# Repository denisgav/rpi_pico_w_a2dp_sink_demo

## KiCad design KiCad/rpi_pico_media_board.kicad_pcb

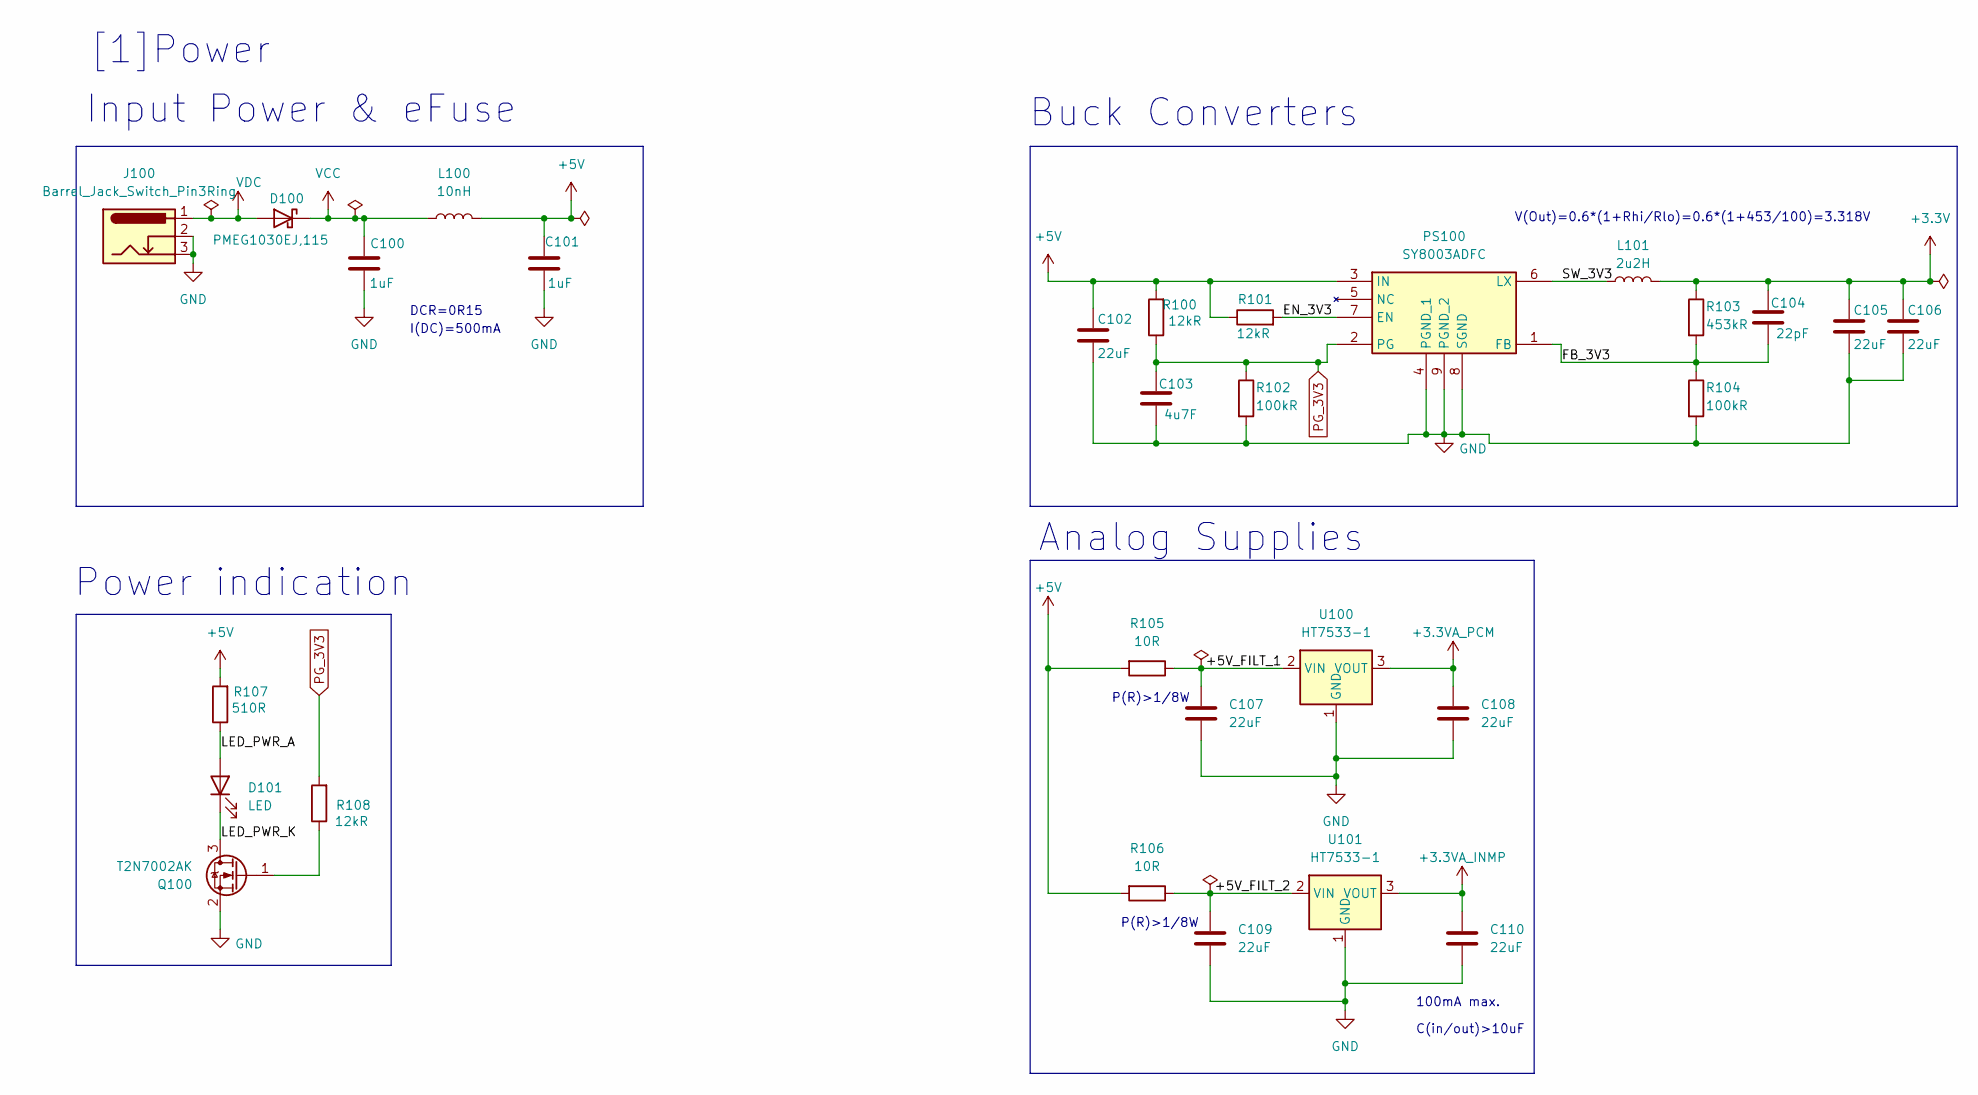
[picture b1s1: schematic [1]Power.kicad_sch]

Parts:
C100, C101: 1uF; C_0603_1608Metric; Manufacturer Part Number CL10A105KB8NNNC
C102, C105, C106, C107, C108, C109, C110: 22uF; C_1206_3216Metric; Manufacturer Part Number CS3216X5R226M160NRI
C103: 4u7F; C_0603_1608Metric; Manufacturer Part Number CL10A475KP8NNNC
C104: 22pF; C_0603_1608Metric; Manufacturer Part Number CL10C220JB8NNNC
D100: PMEG1030EJ,115; D_SOD-323F; Manufacturer Part Number PMEG1030EJ,115
D101: LED; LED_0603_1608Metric; Manufacturer Part Number XL-1608SURC-06
J100: Barrel_Jack_Switch_Pin3Ring; BarrelJack_GCT_DCJ200-10-A_Horizontal; Manufacturer Part Number DC005
L100: 10nH; L_0603_1608Metric; Manufacturer Part Number LQW18AN10NG10D
L101: 2u2H; L_1008_2520Metric; Manufacturer Part Number DFE252012F-2R2M=P2
PS100: SY8003ADFC; SON50P200X200X65-9N; Manufacturer Part Number SY8003ADFC
Q100: T2N7002AK; SOT-23; Manufacturer Part Number T2N7002AK,LM
R100, R101, R108: 12kR; R_0603_1608Metric; Manufacturer Part Number 0603WAF1202T5E
R102, R104: 100kR; R_0603_1608Metric; Manufacturer Part Number 0603WAF1003T5E
R103: 453kR; R_0603_1608Metric; Manufacturer Part Number 0603WAF4533T5E
R105, R106: 10R; R_0805_2012Metric; Manufacturer Part Number 0805W8F100JT5E
R107: 510R; R_0603_1608Metric; Manufacturer Part Number 0603WAF5100T5E
U100, U101: HT7533-1; SOT-89-3; Manufacturer Part Number HT7533-1

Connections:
+3.3V: C104.1, C105.1, C106.1, L101.2, R103.1; also elsewhere on the board
+3.3VA_INMP: C110.1, U101.3 (VOUT); also elsewhere on the board
+3.3VA_PCM: C108.1, U100.3 (VOUT); also elsewhere on the board
+5V: C101.1, C102.1, L100.2, PS100.3 (IN), R100.2, R101.1, R105.2, R106.2, R107.2; also elsewhere on the board
/[1]Power/+5V_FILT_1: C107.1, R105.1, U100.2 (VIN)
/[1]Power/+5V_FILT_2: C109.1, R106.1, U101.2 (VIN)
/[1]Power/EN_3V3: PS100.7 (EN), R101.2
/[1]Power/FB_3V3: C104.2, PS100.1 (FB), R103.2, R104.1
/[1]Power/LED_PWR_A: D101.2 (A), R107.1
/[1]Power/LED_PWR_K: D101.1 (K), Q100.3 (D)
/[1]Power/SW_3V3: L101.1, PS100.6 (LX)
GND: C100.2, C101.2, C102.2, C103.2, C105.2, C106.2, C107.2, C108.2, C109.2, C110.2, J100.2, J100.3, PS100.4 (PGND_1), PS100.8 (SGND), PS100.9 (PGND_2), Q100.2 (S), R102.2, R104.2, U100.1 (GND), U101.1 (GND); also elsewhere on the board
unnamed: Q100.1 (G), R108.1
PG_3V3: C103.1, PS100.2 (PG), R100.1, R102.1, R108.2
VCC: C100.1, D100.1 (K), L100.1; also elsewhere on the board
VDC: D100.2 (A), J100.1

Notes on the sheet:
Analog Supplies
Power indication
P(R)>1/8W
I(DC)=500mA
Input Power & eFuse
100mA max.
[1]Power
DCR=0R15
C(in/out)>10uF
V(Out)=0.6*(1+Rhi/Rlo)=0.6*(1+453/100)=3.318V
Buck Converters

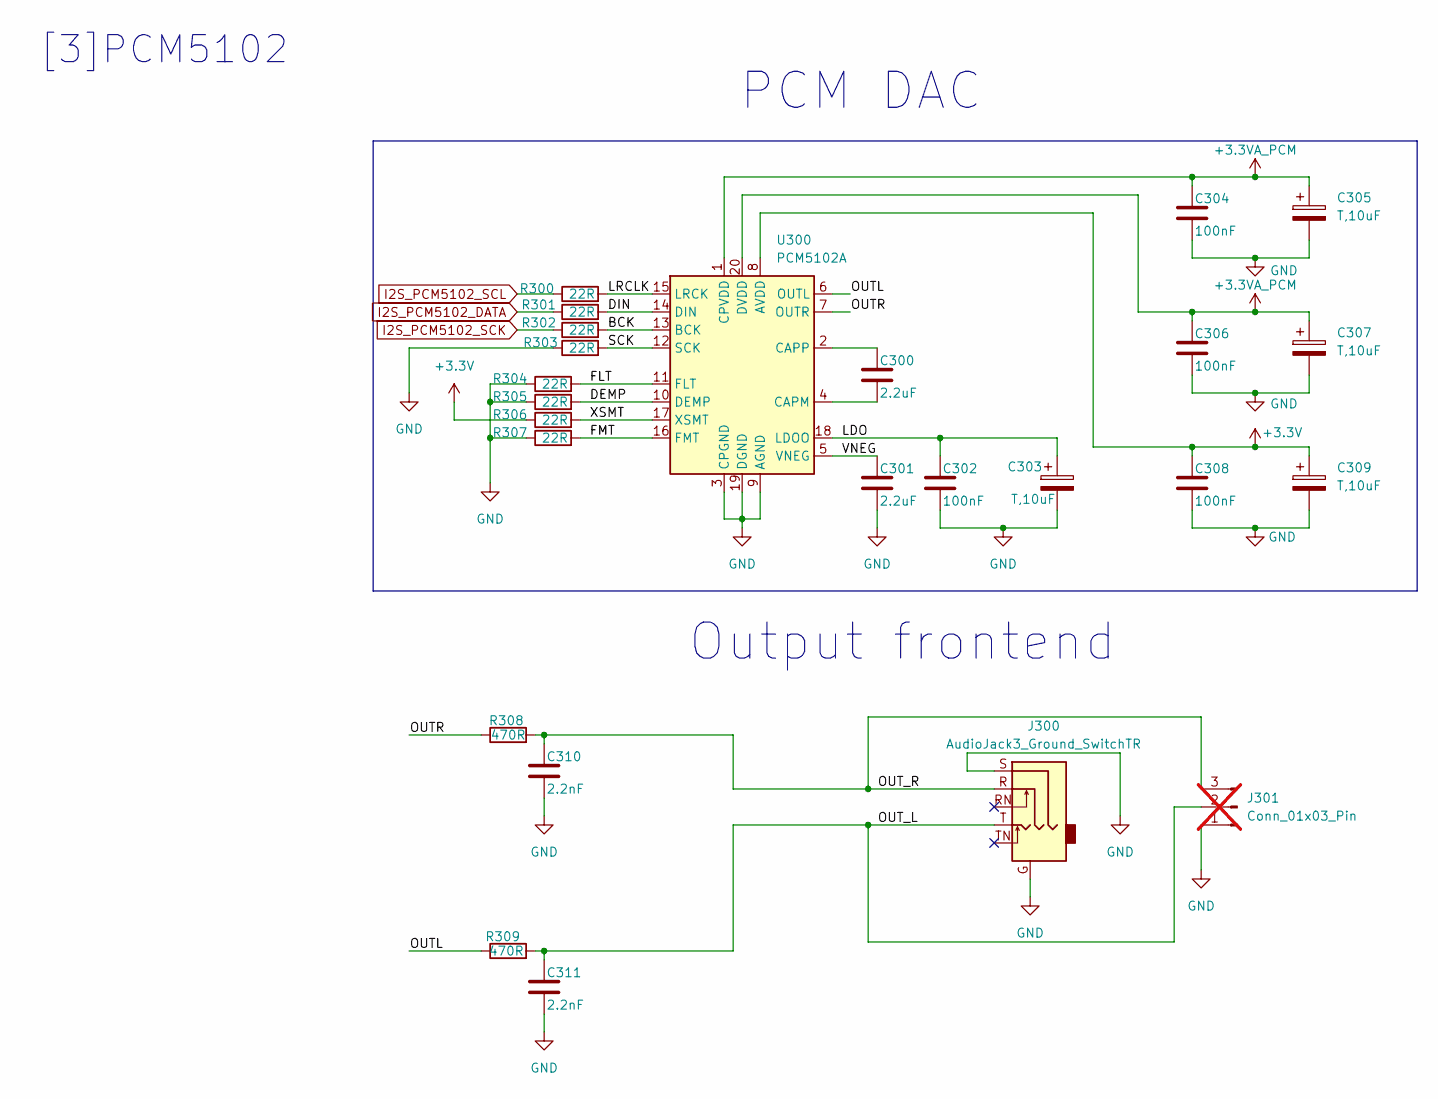
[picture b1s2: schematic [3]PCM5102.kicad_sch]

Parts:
C300, C301: 2.2uF; C_0603_1608Metric; Manufacturer Part Number CL10A225KA8NNNC
C302, C304, C306, C308: 100nF; C_0603_1608Metric; Manufacturer Part Number CL10B104KA8NNNC
C303, C305, C307, C309: T,10uF; CP_EIA-3216-18_Kemet-A; Manufacturer Part Number TAJA106K016RNJ
C310, C311: 2.2nF; C_0603_1608Metric; Manufacturer Part Number CL10B222KB8NNNC
J300: AudioJack3_Ground_SwitchTR; AudioJack_3.5mm_PJ311; Manufacturer Part Number PJ-342
J301: Conn_01x03_Pin; PinHeader_1x03_P2.54mm_Vertical; not fitted
R300, R301, R302, R303, R304, R305, R306, R307: 22R; R_0603_1608Metric; Manufacturer Part Number 0603WAF220JT5E
R308, R309: 470R; R_0805_2012Metric; Manufacturer Part Number ARG05FTC4700
U300: PCM5102A; TSSOP-20_4.4x6.5mm_P0.65mm; Manufacturer Part Number PCM5102AQPWRQ1

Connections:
+3.3V: C308.1, C309.1, R306.1, U300.8 (AVDD); also elsewhere on the board
+3.3VA_PCM: C304.1, C305.1, C306.1, C307.1, U300.1 (CPVDD), U300.20 (DVDD); also elsewhere on the board
/[3]PCM5102/BCK: R302.2, U300.13 (BCK)
/[3]PCM5102/DEMP: R305.2, U300.10 (DEMP)
/[3]PCM5102/DIN: R301.2, U300.14 (DIN)
/[3]PCM5102/FLT: R304.2, U300.11 (FLT)
/[3]PCM5102/FMT: R307.2, U300.16 (FMT)
/[3]PCM5102/LDO: C302.1, C303.1, U300.18 (LDOO)
/[3]PCM5102/LRCLK: R300.2, U300.15 (LRCK)
/[3]PCM5102/OUTL: R309.1, U300.6 (OUTL)
/[3]PCM5102/OUTR: R308.1, U300.7 (OUTR)
/[3]PCM5102/OUT_L: C311.1, J300.T, J301.2, R309.2
/[3]PCM5102/OUT_R: C310.1, J300.R, J301.3, R308.2
/[3]PCM5102/SCK: R303.2, U300.12 (SCK)
/[3]PCM5102/VNEG: C301.1, U300.5 (VNEG)
/[3]PCM5102/XSMT: R306.2, U300.17 (XSMT)
GND: C301.2, C302.2, C303.2, C304.2, C305.2, C306.2, C307.2, C308.2, C309.2, C310.2, C311.2, J300.G, J300.S, J301.1, R303.1, R304.1, R305.1, R307.1, U300.3 (CPGND), U300.9 (AGND), U300.19 (DGND); also elsewhere on the board
I2S_PCM5102_DATA: R301.1; also elsewhere on the board
I2S_PCM5102_SCK: R302.1; also elsewhere on the board
I2S_PCM5102_SCL: R300.1; also elsewhere on the board
unnamed: C300.2, U300.4 (CAPM)
unnamed: C300.1, U300.2 (CAPP)

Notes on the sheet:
[3]PCM5102
Output frontend
PCM DAC

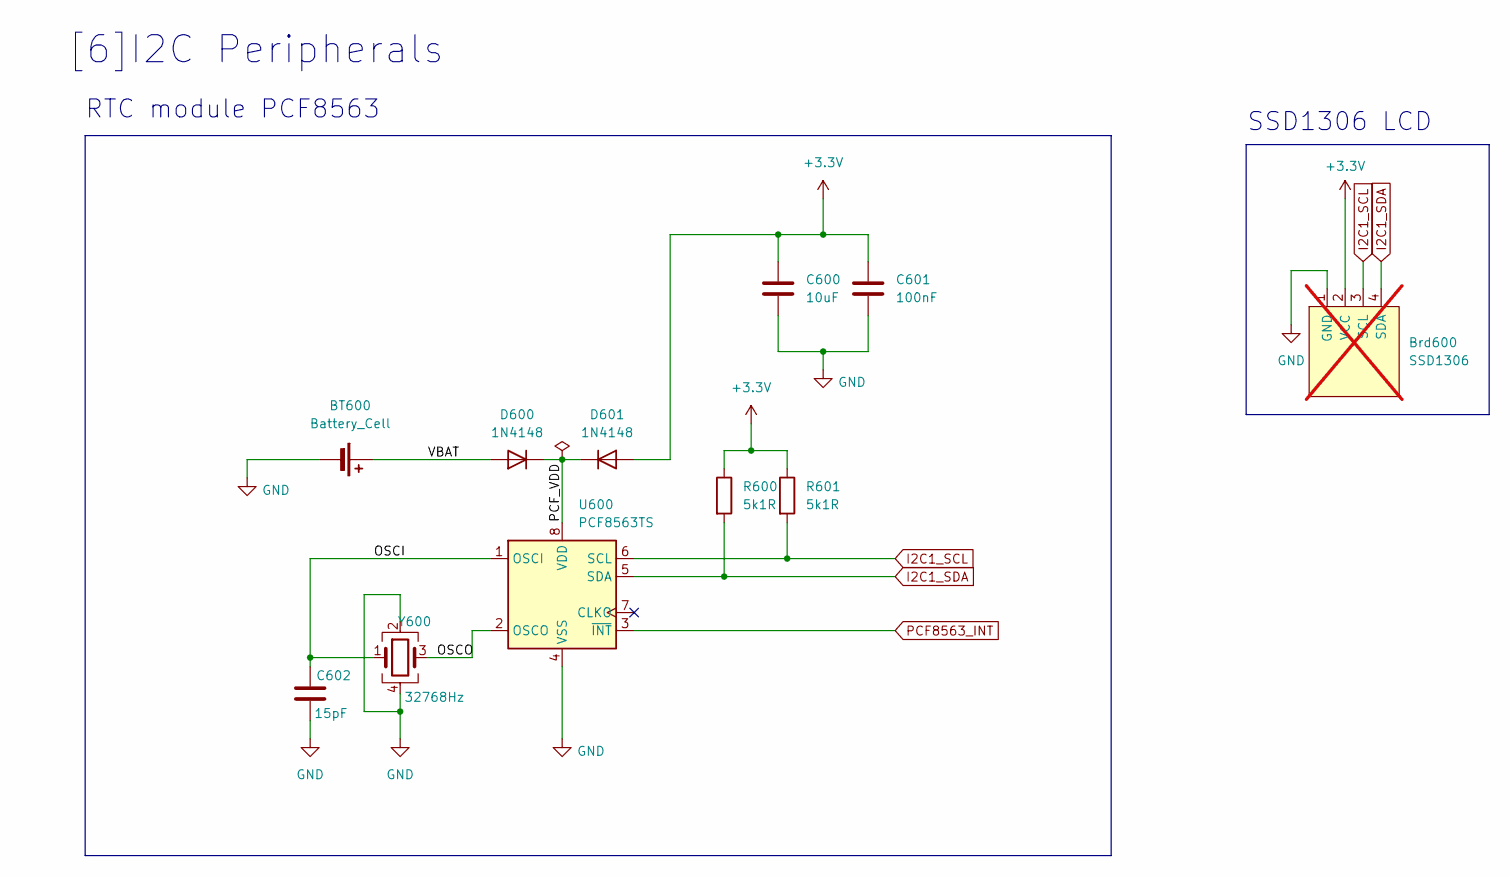
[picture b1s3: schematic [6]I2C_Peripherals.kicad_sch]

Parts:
BT600: Battery_Cell; CR12202; Manufacturer Part Number CR1220-2
Brd600: SSD1306; 128x64OLED; not fitted
C600: 10uF; C_0603_1608Metric; Manufacturer Part Number CL10A106KP8NNNC
C601: 100nF; C_0603_1608Metric; Manufacturer Part Number CL10B104KA8NNNC
C602: 15pF; C_0603_1608Metric; Manufacturer Part Number CL10C150JB8NNNC; DigiKey Part Number 490-11191-6-ND
D600, D601: 1N4148; D_SOD-123; Manufacturer Part Number 1N4148W
R600, R601: 5k1R; R_0805_2012Metric; Manufacturer Part Number 0805W8F5101T5E
U600: PCF8563TS; MSOP-8_3x3mm_P0.65mm; Manufacturer Part Number PCF8563TS/5,118
Y600: 32768Hz; Crystal_SMD_3225-4Pin_3.2x2.5mm; Manufacturer Part Number OK2EL89CJI-111YLC-32.768K; DigiKey Part Number 535-ASEK-32.768KHZ-L-R-TDKR-ND

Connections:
+3.3V: Brd600.2 (VCC), C600.1, C601.1, D601.2 (A), R600.1, R601.1; also elsewhere on the board
/[6]I2C_Peripherals/OSCI: C602.1, U600.1 (OSCI), Y600.1
/[6]I2C_Peripherals/OSCO: U600.2 (OSCO), Y600.3
/[6]I2C_Peripherals/PCF_VDD: D600.1 (K), D601.1 (K), U600.8 (VDD)
/[6]I2C_Peripherals/VBAT: BT600.1 (+), D600.2 (A)
GND: BT600.2 (-), Brd600.1 (GND), C600.2, C601.2, C602.2, U600.4 (VSS), Y600.2, Y600.4; also elsewhere on the board
I2C1_SCL: Brd600.3 (SCL), R601.2, U600.6 (SCL); also elsewhere on the board
I2C1_SDA: Brd600.4 (SDA), R600.2, U600.5 (SDA); also elsewhere on the board
PCF8563_INT: U600.3 (~INT); also elsewhere on the board

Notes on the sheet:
[6]I2C Peripherals
SSD1306 LCD
RTC module PCF8563

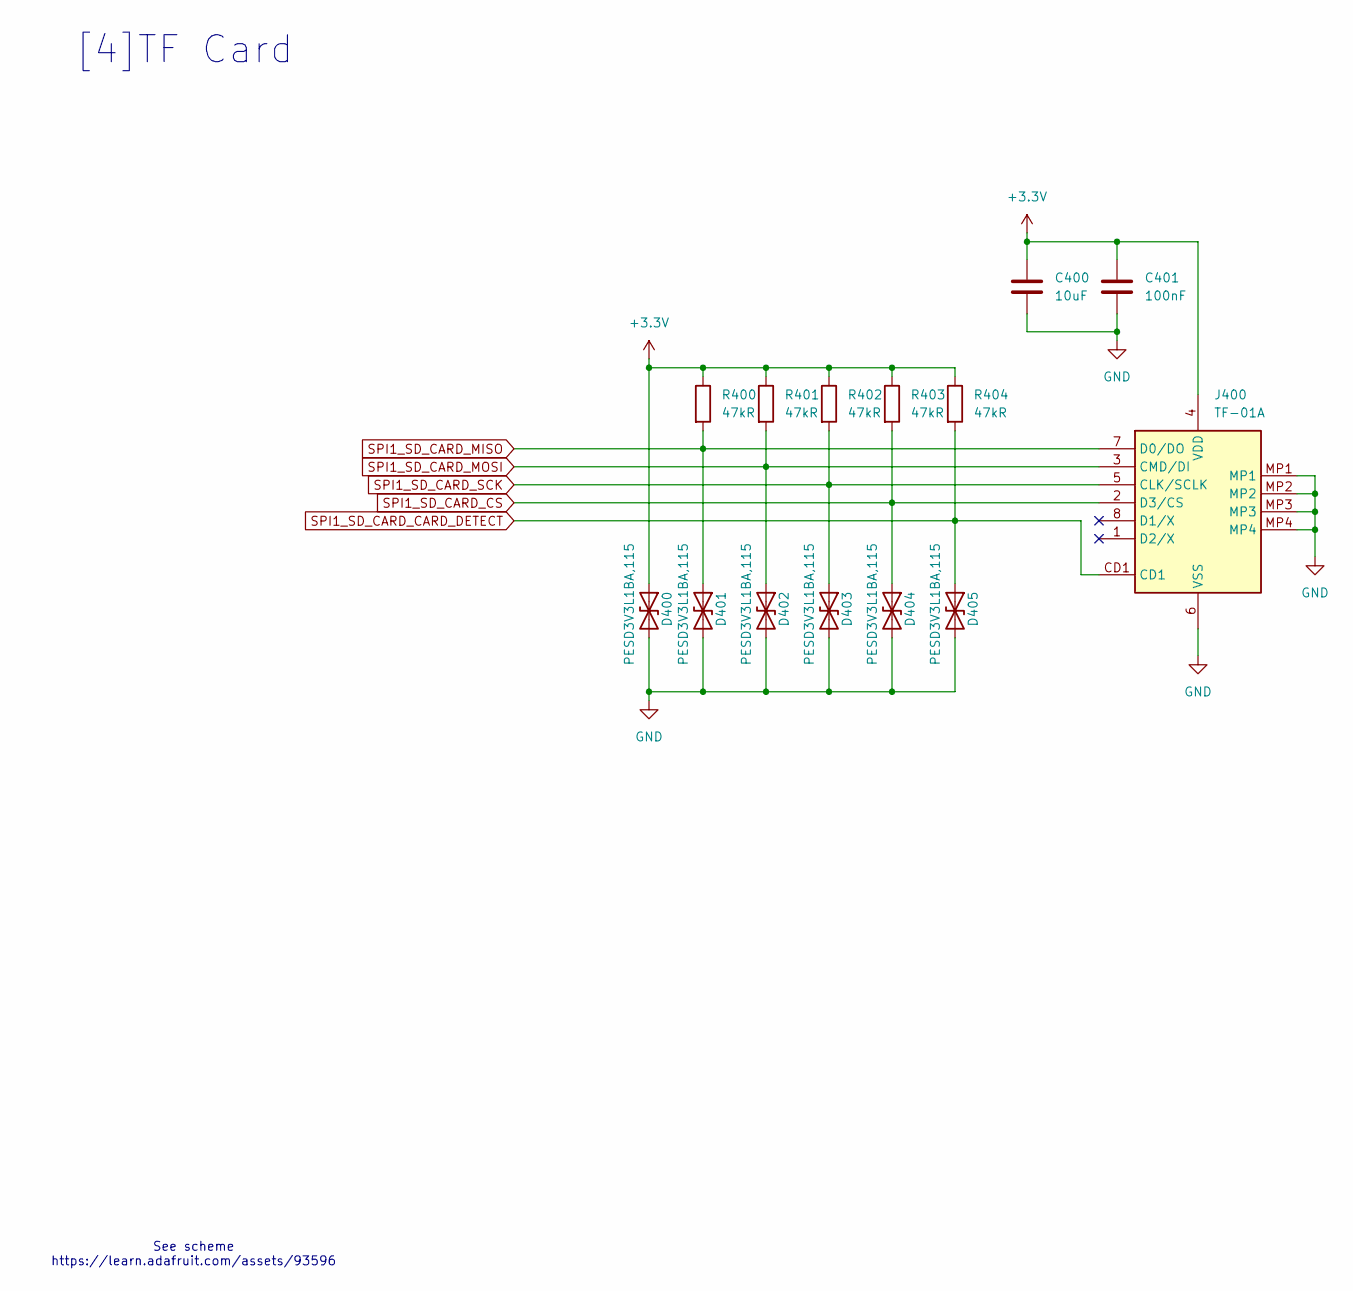
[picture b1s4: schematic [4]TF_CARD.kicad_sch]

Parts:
C400: 10uF; C_0603_1608Metric; Manufacturer Part Number CL10A106KP8NNNC
C401: 100nF; C_0603_1608Metric; Manufacturer Part Number CL10B104KA8NNNC
D400, D401, D402, D403, D404, D405: PESD3V3L1BA,115; D_SOD-323; Manufacturer Part Number PESD3V3L1BA,115
J400: TF-01A; TF01A; Manufacturer Part Number TF-01A
R400, R401, R402, R403, R404: 47kR; R_0603_1608Metric; Manufacturer Part Number 0603WAJ0473T5E

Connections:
+3.3V: C400.1, C401.1, D400.1 (A1), J400.4 (VDD), R400.1, R401.1, R402.1, R403.1, R404.1; also elsewhere on the board
GND: C400.2, C401.2, D400.2 (A2), D401.2 (A2), D402.2 (A2), D403.2 (A2), D404.2 (A2), D405.2 (A2), J400.6 (VSS), J400.MP1, J400.MP2, J400.MP3, J400.MP4; also elsewhere on the board
SPI1_SD_CARD_CARD_DETECT: D405.1 (A1), J400.CD1, R404.2; also elsewhere on the board
SPI1_SD_CARD_CS: D404.1 (A1), J400.2 (D3/CS), R403.2; also elsewhere on the board
SPI1_SD_CARD_MISO: D401.1 (A1), J400.7 (D0/DO), R400.2; also elsewhere on the board
SPI1_SD_CARD_MOSI: D402.1 (A1), J400.3 (CMD/DI), R401.2; also elsewhere on the board
SPI1_SD_CARD_SCK: D403.1 (A1), J400.5 (CLK/SCLK), R402.2; also elsewhere on the board

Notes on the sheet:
See scheme https://learn.adafruit.com/assets/93596
[4]TF Card

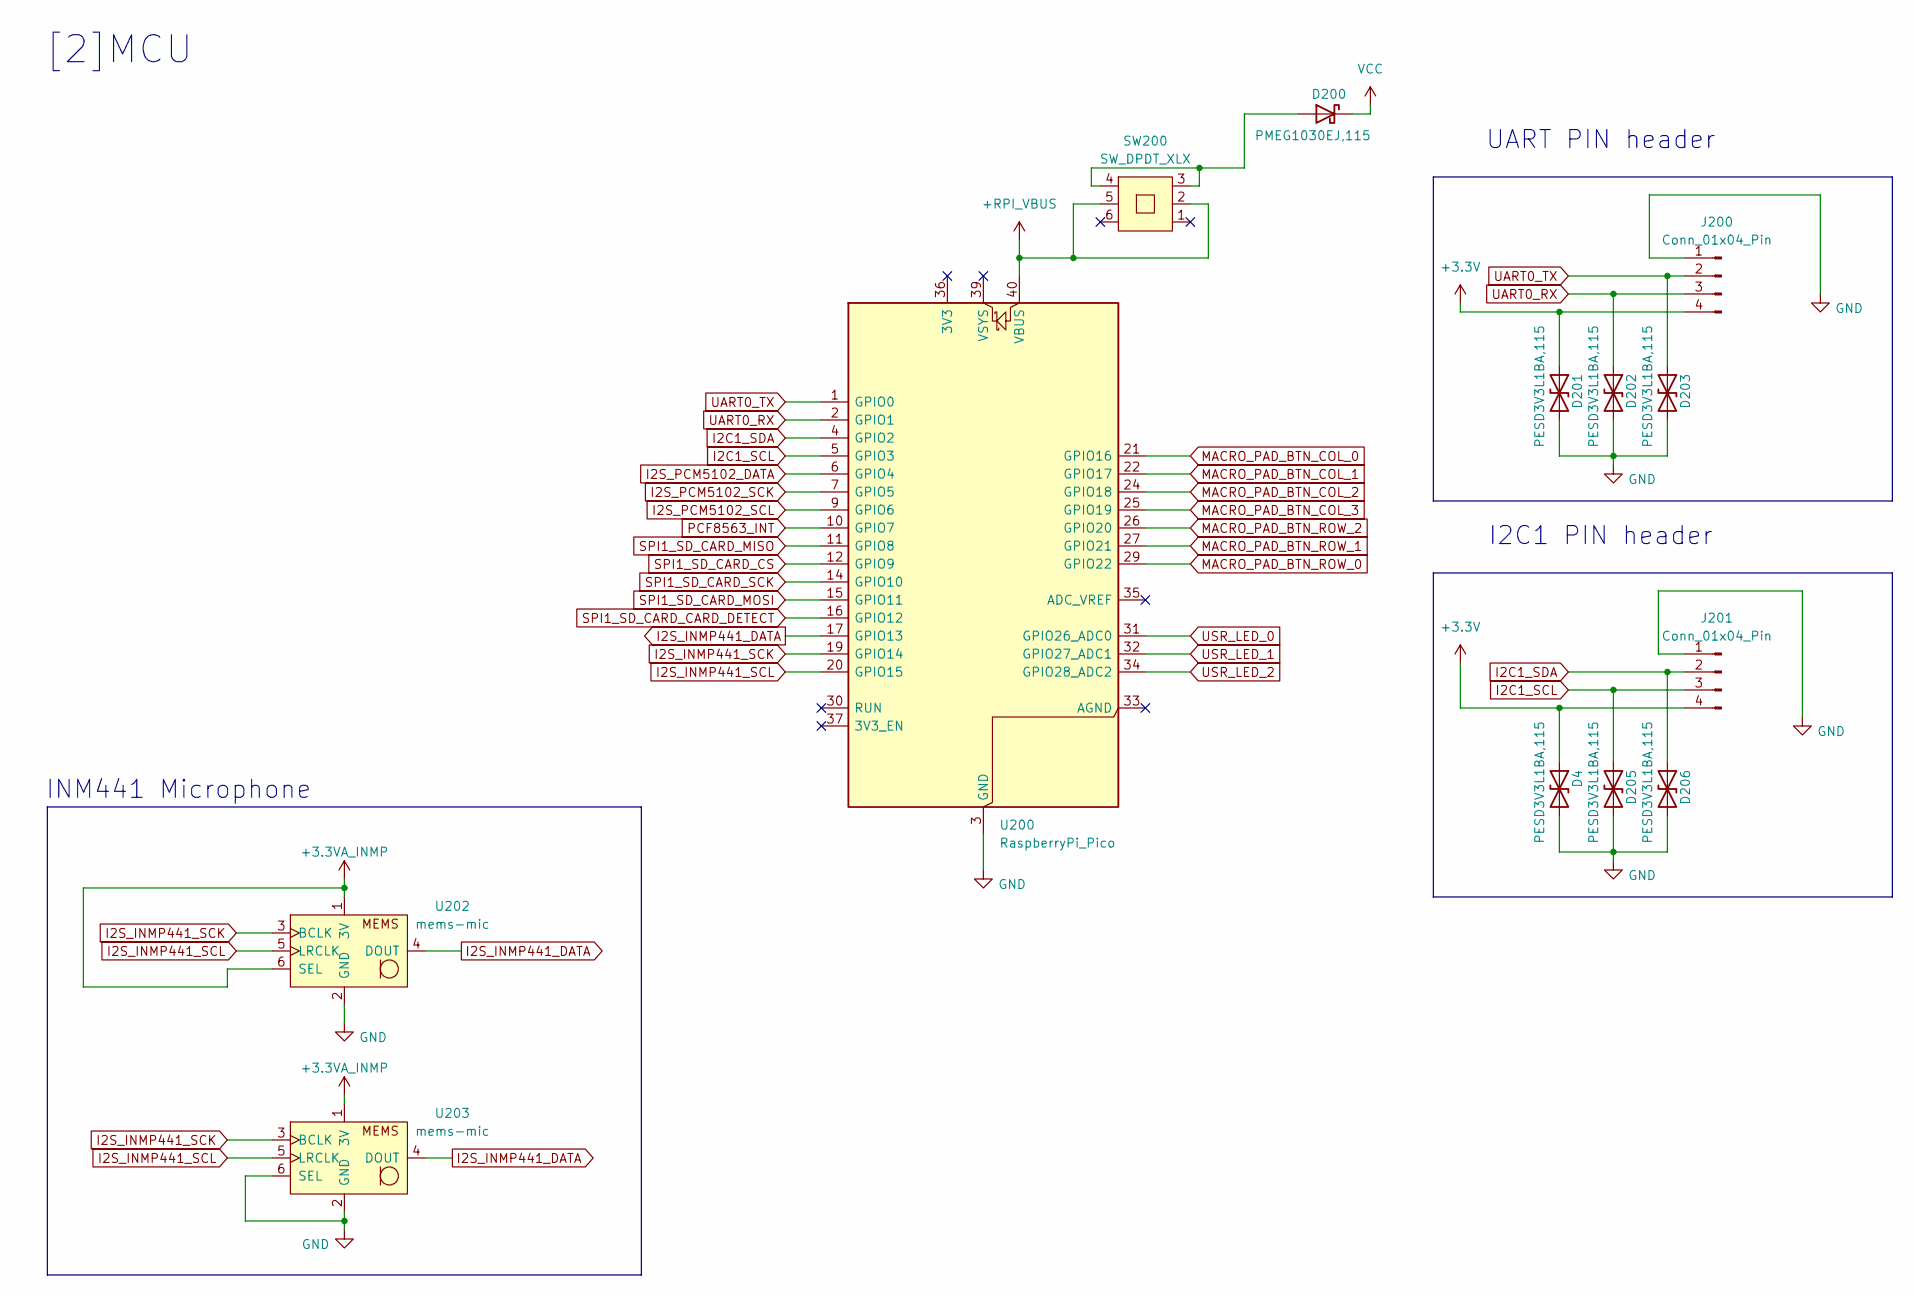
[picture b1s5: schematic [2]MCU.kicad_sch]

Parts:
D4, D201, D202, D203, D205, D206: PESD3V3L1BA,115; D_SOD-323; Manufacturer Part Number PESD3V3L1BA,115
D200: PMEG1030EJ,115; D_SOD-323F; Manufacturer Part Number PMEG1030EJ,115
J200, J201: Conn_01x04_Pin; PinHeader_1x04_P2.54mm_Vertical
SW200: SW_DPDT_XLX
U200: RaspberryPi_Pico; RaspberryPi_Pico_Common_THT
U202, U203: mems-mic; inmp441

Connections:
+3.3V: D4.1 (A1), D201.1 (A1), J200.4, J201.4; also elsewhere on the board
+3.3VA_INMP: U202.1 (3V), U202.6 (SEL), U203.1 (3V); also elsewhere on the board
+RPI_VBUS: SW200.2, SW200.5, U200.40 (VBUS)
GND: D4.2 (A2), D201.2 (A2), D202.2 (A2), D203.2 (A2), D205.2 (A2), D206.2 (A2), J200.1, J201.1, U200.3 (GND), U200.8 (GND), U200.13 (GND), U200.18 (GND), U200.23 (GND), U200.28 (GND), U200.38 (GND), U202.2 (GND), U203.2 (GND), U203.6 (SEL); also elsewhere on the board
I2C1_SCL: D205.1 (A1), J201.3, U200.5 (GPIO3); also elsewhere on the board
I2C1_SDA: D206.1 (A1), J201.2, U200.4 (GPIO2); also elsewhere on the board
I2S_INMP441_DATA: U200.17 (GPIO13), U202.4 (DOUT), U203.4 (DOUT)
I2S_INMP441_SCK: U200.19 (GPIO14), U202.3 (BCLK), U203.3 (BCLK)
I2S_INMP441_SCL: U200.20 (GPIO15), U202.5 (LRCLK), U203.5 (LRCLK)
I2S_PCM5102_DATA: U200.6 (GPIO4); also elsewhere on the board
I2S_PCM5102_SCK: U200.7 (GPIO5); also elsewhere on the board
I2S_PCM5102_SCL: U200.9 (GPIO6); also elsewhere on the board
MACRO_PAD_BTN_COL_0: U200.21 (GPIO16); also elsewhere on the board
MACRO_PAD_BTN_COL_1: U200.22 (GPIO17); also elsewhere on the board
MACRO_PAD_BTN_COL_2: U200.24 (GPIO18); also elsewhere on the board
MACRO_PAD_BTN_COL_3: U200.25 (GPIO19); also elsewhere on the board
MACRO_PAD_BTN_ROW_0: U200.29 (GPIO22); also elsewhere on the board
MACRO_PAD_BTN_ROW_1: U200.27 (GPIO21); also elsewhere on the board
MACRO_PAD_BTN_ROW_2: U200.26 (GPIO20); also elsewhere on the board
unnamed: D200.2 (A), SW200.3, SW200.4
PCF8563_INT: U200.10 (GPIO7); also elsewhere on the board
SPI1_SD_CARD_CARD_DETECT: U200.16 (GPIO12); also elsewhere on the board
SPI1_SD_CARD_CS: U200.12 (GPIO9); also elsewhere on the board
SPI1_SD_CARD_MISO: U200.11 (GPIO8); also elsewhere on the board
SPI1_SD_CARD_MOSI: U200.15 (GPIO11); also elsewhere on the board
SPI1_SD_CARD_SCK: U200.14 (GPIO10); also elsewhere on the board
UART0_RX: D202.1 (A1), J200.3, U200.2 (GPIO1)
UART0_TX: D203.1 (A1), J200.2, U200.1 (GPIO0)
USR_LED_0: U200.31 (GPIO26_ADC0); also elsewhere on the board
USR_LED_1: U200.32 (GPIO27_ADC1); also elsewhere on the board
USR_LED_2: U200.34 (GPIO28_ADC2); also elsewhere on the board
VCC: D200.1 (K); also elsewhere on the board

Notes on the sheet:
INM441 Microphone
UART PIN header
I2C1 PIN header
[2]MCU

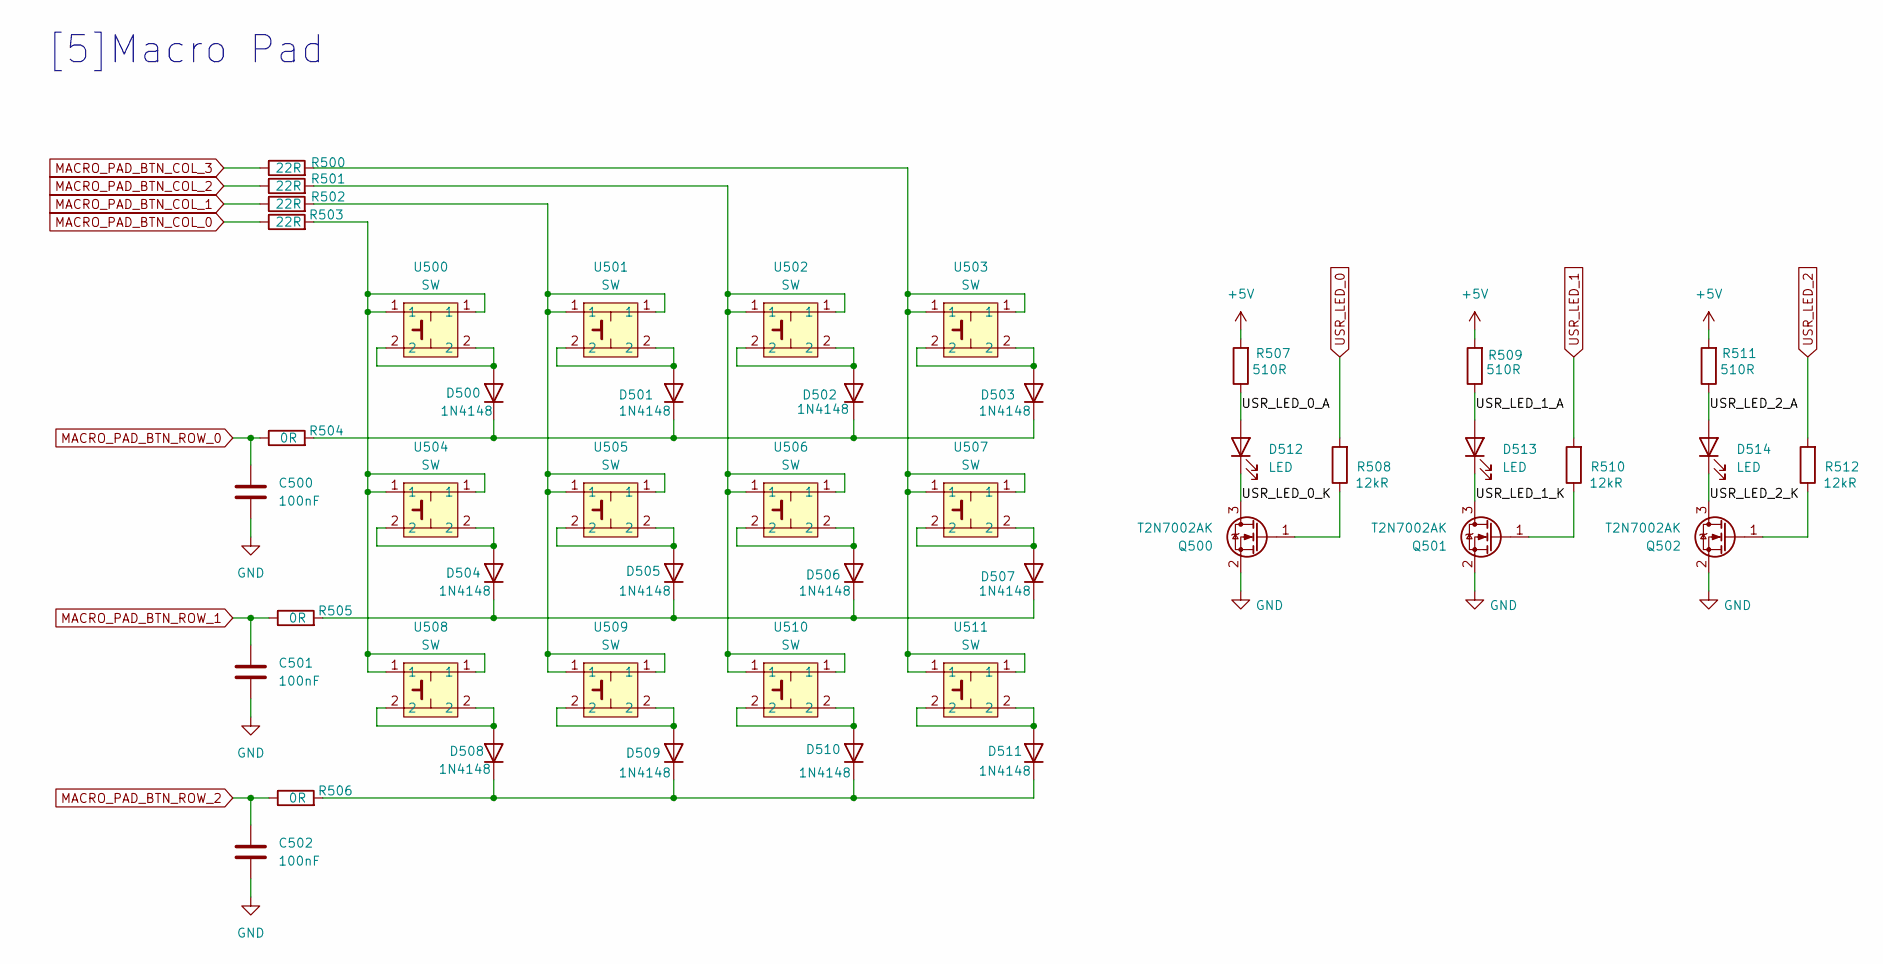
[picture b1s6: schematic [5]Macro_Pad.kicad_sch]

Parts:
C500, C501, C502: 100nF; C_0603_1608Metric; Manufacturer Part Number CL10B104KA8NNNC
D500, D501, D502, D503, D504, D505, D506, D507, D508, D509, D510, D511: 1N4148; D_SOD-123; Manufacturer Part Number 1N4148W
D512, D513, D514: LED; LED_0603_1608Metric; Manufacturer Part Number XL-1608SURC-06
Q500, Q501, Q502: T2N7002AK; SOT-23; Manufacturer Part Number T2N7002AK,LM
R500, R501, R502, R503: 22R; R_0603_1608Metric; Manufacturer Part Number 0603WAF220JT5E
R504, R505, R506: 0R; R_0603_1608Metric; Manufacturer Part Number 0603WAF0000T5E
R507, R509, R511: 510R; R_0603_1608Metric; Manufacturer Part Number 0603WAF5100T5E
R508, R510, R512: 12kR; R_0603_1608Metric; Manufacturer Part Number 0603WAF1202T5E
U500, U501, U502, U503, U504, U505, U506, U507, U508, U509, U510, U511: SW; SW_PUSH_6mm_H5mm; Manufacturer Part Number SMG-01-H080A1

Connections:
+5V: R507.2, R509.2, R511.2; also elsewhere on the board
/[5]Macro_Pad/USR_LED_0_A: D512.2 (A), R507.1
/[5]Macro_Pad/USR_LED_0_K: D512.1 (K), Q500.3 (D)
/[5]Macro_Pad/USR_LED_1_A: D513.2 (A), R509.1
/[5]Macro_Pad/USR_LED_1_K: D513.1 (K), Q501.3 (D)
/[5]Macro_Pad/USR_LED_2_A: D514.2 (A), R511.1
/[5]Macro_Pad/USR_LED_2_K: D514.1 (K), Q502.3 (D)
GND: C500.2, C501.2, C502.2, Q500.2 (S), Q501.2 (S), Q502.2 (S); also elsewhere on the board
MACRO_PAD_BTN_COL_0: R503.1; also elsewhere on the board
MACRO_PAD_BTN_COL_1: R502.1; also elsewhere on the board
MACRO_PAD_BTN_COL_2: R501.1; also elsewhere on the board
MACRO_PAD_BTN_COL_3: R500.1; also elsewhere on the board
MACRO_PAD_BTN_ROW_0: C500.1, R504.1; also elsewhere on the board
MACRO_PAD_BTN_ROW_1: C501.1, R505.1; also elsewhere on the board
MACRO_PAD_BTN_ROW_2: C502.1, R506.1; also elsewhere on the board
unnamed: D500.2 (A), U500.2
unnamed: D500.1 (K), D501.1 (K), D502.1 (K), D503.1 (K), R504.2
unnamed: D501.2 (A), U501.2
unnamed: D502.2 (A), U502.2
unnamed: D503.2 (A), U503.2
unnamed: D504.2 (A), U504.2
unnamed: D504.1 (K), D505.1 (K), D506.1 (K), D507.1 (K), R505.2
unnamed: D505.2 (A), U505.2
unnamed: D506.2 (A), U506.2
unnamed: D507.2 (A), U507.2
unnamed: D508.2 (A), U508.2
unnamed: D508.1 (K), D509.1 (K), D510.1 (K), D511.1 (K), R506.2
unnamed: D509.2 (A), U509.2
unnamed: D510.2 (A), U510.2
unnamed: D511.2 (A), U511.2
unnamed: Q500.1 (G), R508.1
unnamed: Q501.1 (G), R510.1
unnamed: Q502.1 (G), R512.1
unnamed: R500.2, U503.1, U507.1, U511.1
unnamed: R501.2, U502.1, U506.1, U510.1
unnamed: R502.2, U501.1, U505.1, U509.1
unnamed: R503.2, U500.1, U504.1, U508.1
USR_LED_0: R508.2; also elsewhere on the board
USR_LED_1: R510.2; also elsewhere on the board
USR_LED_2: R512.2; also elsewhere on the board

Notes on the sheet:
[5]Macro Pad

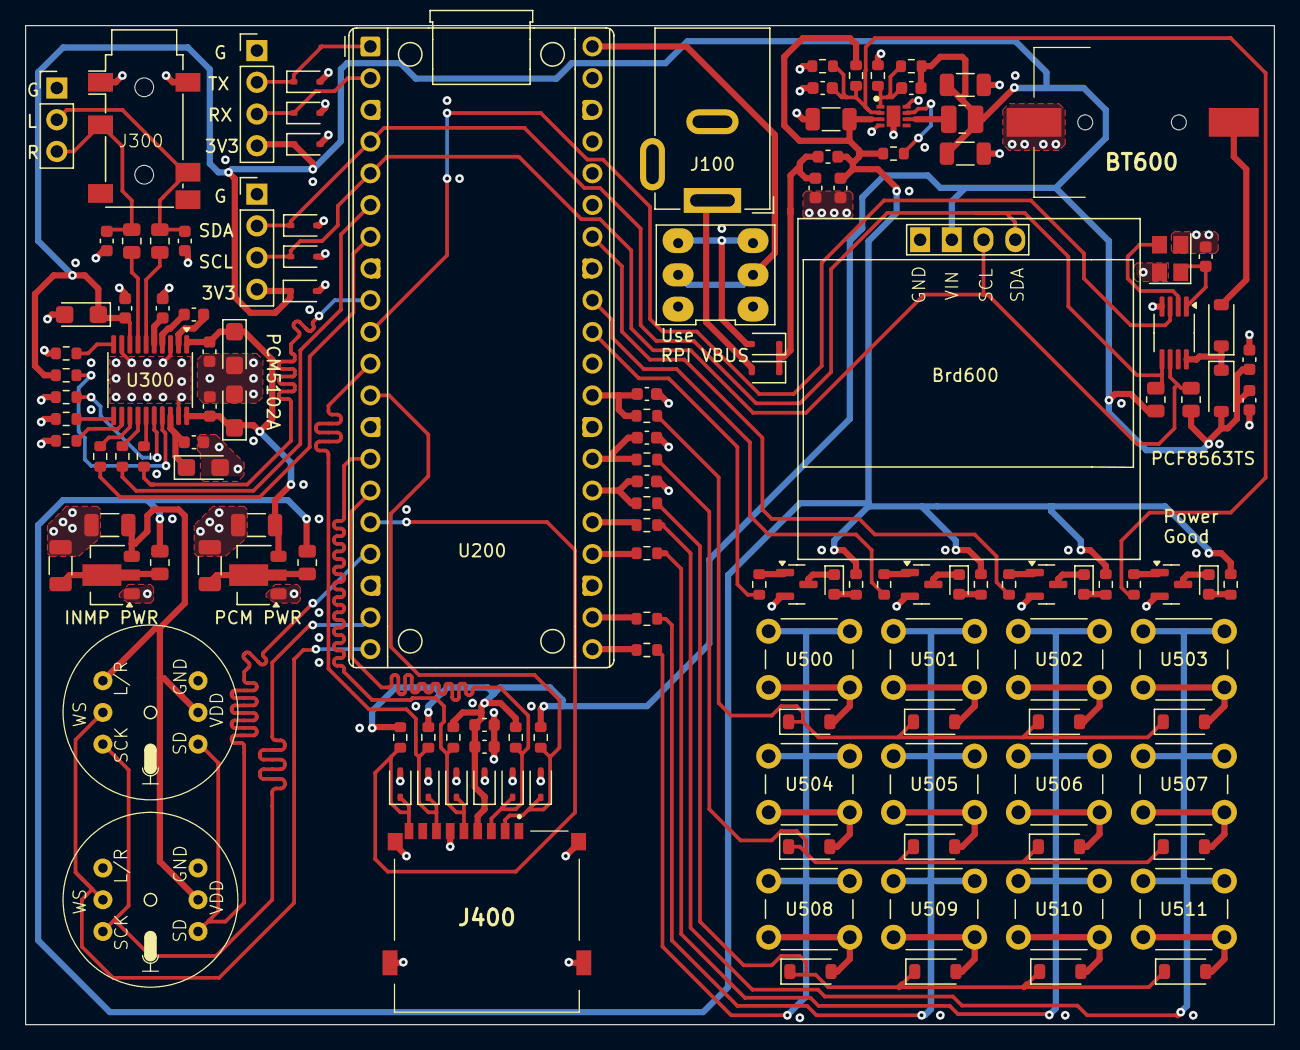
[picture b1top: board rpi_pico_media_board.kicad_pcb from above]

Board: 4 copper layers, 100.0 x 80.0 mm, 138 parts (0 on the bottom side), 92 nets.

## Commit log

2025-03-21 Simplified CmakeList
2025-03-21 Simplify CMake files
2025-03-23 Cmake file fixes
2025-03-26 Simplify example
2025-03-26 Add FreeRTOS library. Initial board pinout
2025-03-28 FreeRTOS integration fixes
2025-03-29 Add buttons handle function
2025-03-29 Add button handling function
2025-03-29 Volume apply
2025-03-31 Add more buttons. Update pinout
2025-04-03 Add code for SD Card test
2025-04-04 Add SSD1306 LCD
2025-04-05 Scheme initial commit
2025-04-05 Scheme improvements
2025-04-05 Minor BOM updates
2025-04-05 DRC cleanup
2025-04-06 PCB initial placement
2025-04-07 Very initial PCB layout
2025-04-07 minor layout update
2025-04-07 PCB initial layout
2025-04-07 Macro Pad routing
2025-04-08 SD Card routing
2025-04-08 Initial PCB version
2025-04-09 Minor PCB layout updates
2025-04-09 Trace length tuning
2025-04-21 Update directory structure
2025-04-21 Add USB speaker and microphone
2025-04-22 Add FreeRTOS library to USB speaker and microphone app
2025-04-23 first unstable pcf8563 library
2025-04-24 SD Card example
2025-04-26 Manufacture files preparation
2025-04-26 Manufacture files
2025-04-27 Initial usb_uac2_headset firmware
2025-04-27 Add microphone to usb_uac2_headset example
2025-04-27 Add keypad handling
2025-05-01 pcf8532 improvements
2025-05-01 update status led indication
2025-05-01 First try to add USB HID media control
2025-05-03 keypad app updates
2025-05-18 First fixes after board assembly
2025-05-19 Fixes for mic sample rate configuration
2025-05-20 A2DP example integration
2025-05-21 Simplify A2DP CMake file
2025-05-22 Fix firmware for windows
2025-05-23 Stereo microphone support
2025-05-23 Use separate clocks for microphone and speaker
2025-05-24 Add UAC2+HID combined firmware
2025-06-01 USB MSC app first commit
2025-06-01 First try to run USB MSC app
2025-06-01 Minor SD MMC optimization
